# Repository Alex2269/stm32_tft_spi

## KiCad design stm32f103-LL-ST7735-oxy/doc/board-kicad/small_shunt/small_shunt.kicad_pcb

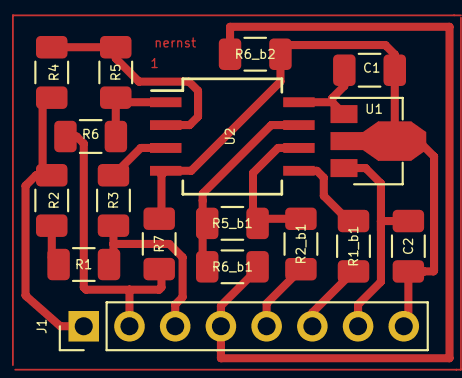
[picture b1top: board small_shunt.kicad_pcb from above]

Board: 2 copper layers, 17 parts (0 on the bottom side), 16 nets.

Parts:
C1, C2: C_Small; R_1206_3216Metric
J1: Conn_01x08; PinHeader_1x08_P2.54mm_Vertical
R1, R1_b1, R2, R2_b1, R3, R4, R5, R5_b1, R6, R6_b1, R6_b2, R7: R; R_1206_3216Metric
U1: L78L33_SOT89; SOT-89-3
U2: MCP602; SO-8_5.3x6.2mm_P1.27mm

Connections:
GND: C1.2, C2.2, J1.8, R6_b2.1, R7.1, U1.2, U2.4
unnamed: C1.1, U1.1, U2.8
unnamed: C2.1, J1.7, U1.3
unnamed: J1.1, R2.1, R4.2
unnamed: J1.2, R6.1, R7.2
unnamed: J1.3, R1.2, R3.2
unnamed: J1.4, R6_b1.1, R6_b2.2
unnamed: J1.5, R2_b1.2
unnamed: J1.6, R1_b1.2
unnamed: R1.1, R2.2
unnamed: R1_b1.1, U2.5
unnamed: R2_b1.1, R5_b1.1, U2.6
unnamed: R3.1, U2.3
unnamed: R4.1, R5.2, U2.2
unnamed: R5.1, R6.2, U2.1
unnamed: R5_b1.2, R6_b1.2, U2.7

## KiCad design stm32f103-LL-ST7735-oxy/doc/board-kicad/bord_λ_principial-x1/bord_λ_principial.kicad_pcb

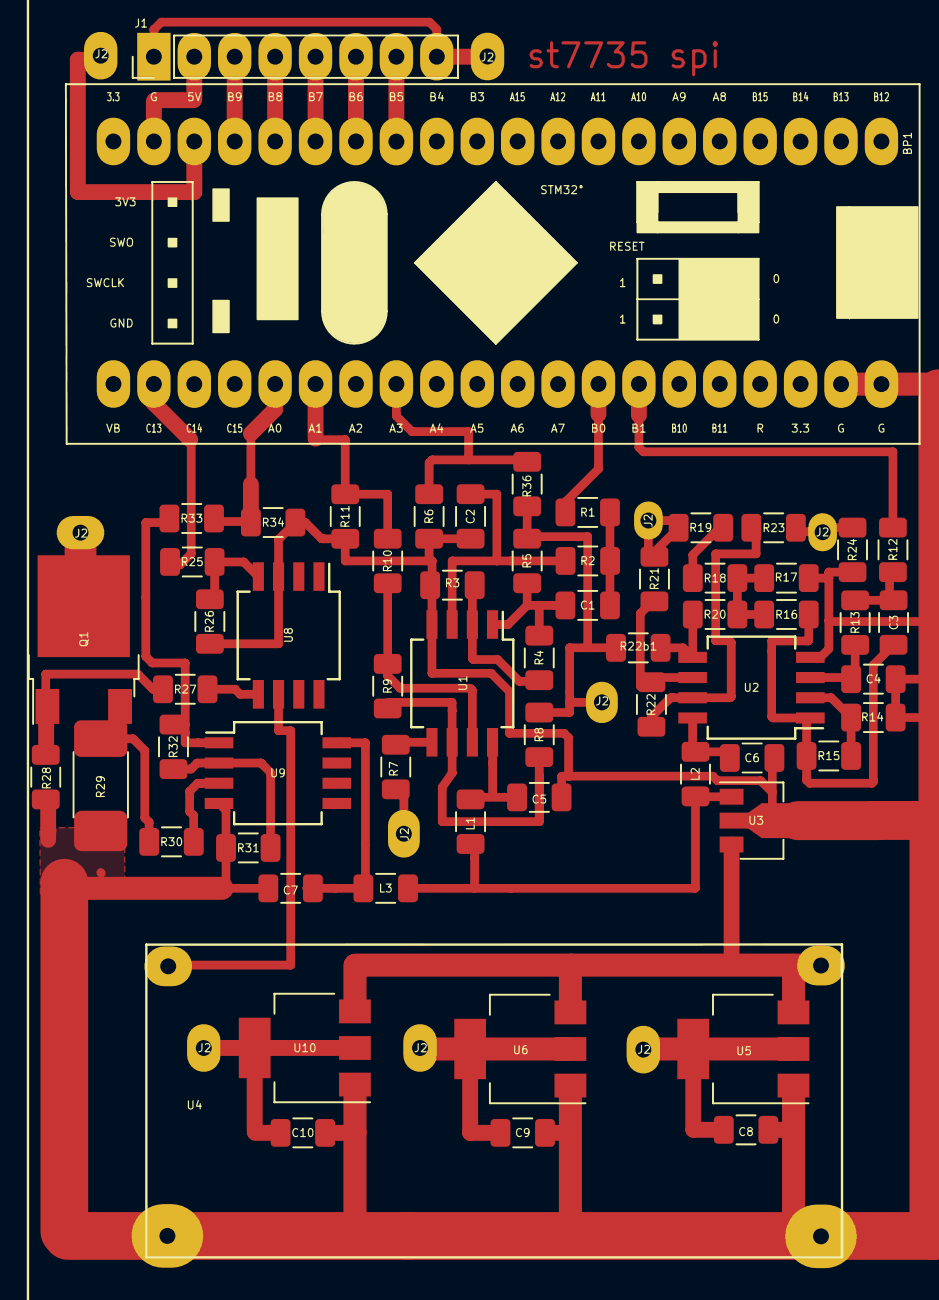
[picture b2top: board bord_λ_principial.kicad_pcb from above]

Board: 2 copper layers, 71 parts (0 on the bottom side), 48 nets.

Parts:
BP1: BluePill_1; YAAJ_BluePill
C1, C2, C3, C4: 1mf; R_1206_3216Metric
C5, C6, C7, C8, C9, C10: 1uF; R_1206_3216Metric
J1: Conn_01x08_Male; PinHeader_1x08_P2.54mm_Vertical
J2, J2#2, J2#3, J2#4, J2#5, J2#6, J2#7, J2#8, J2#9, J2#10: Conn_01x01_Female; MountingHole_2.2mm_M2_DIN965_Pad
L1, L2, L3: 10uG; L_1206_3216Metric
Q1: LR7843; TO-252-2
R1, R2, R3, R7, R8, R12, R13, R14, R20, R21: 43k; R_1206_3216Metric
R4, R6, R15, R17, R26, R28, R36: 22k; R_1206_3216Metric
R5: 10; R_1206_3216Metric
R9: 100; R_1206_3216Metric
R10, R23, R33: 3k3; R_1206_3216Metric
R11, R24, R34: 6k8; R_1206_3216Metric
R16: 240R; R_1206_3216Metric
R18, R19: 31R; R_1206_3216Metric
R22, R22b1: 100k*; R_1206_3216Metric
R25: 1K; R_1206_3216Metric
R27: 0.1K; R_1206_3216Metric
R29: 0.01R; R_2512_6332Metric
R30: 1k; R_1206_3216Metric
R31: 1k*; R_1206_3216Metric
R32: 47k; R_1206_3216Metric
U1, U2, U9: MCP602; SO-8_5.3x6.2mm_P1.27mm
U3: L78L05_SOT89; SOT-89-3
U4: lm2596-hw-411
U5: AMS1117-3.3; SOT-223-3_TabPin2
U6: AMS1117-5.0; SOT-223-3_TabPin2
U8: IR4427; SO-8_5.3x6.2mm_P1.27mm
U10: LM1117-2.5; SOT-223-3_TabPin2

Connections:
+2V5: C10.2, U10.2
+3V3: C8.2, J1.1, J1.8, U5.2
+5P: L1.1, L2.1, L3.1, U3.1
+5V: BP1.18, C9.2, U6.2
+7.5V: U3.3, U4.3, U5.3, U6.3, U10.3
+12V: U4.1, U8.6
GND: BP1.39, BP1.40, C2.1, C4.1, C5.1, C6.1, C7.1, C8.1, C9.1, C10.1, R3.1, R6.1, R11.2, R14.1, R17.1, R24.2, R26.2, R28.2, R29.2, R31.2, R34.1, U1.4, U2.4, U3.2, U4.2, U4.4, U5.1, U6.1, U8.3, U9.4, U10.1
unnamed: BP1.13, J1.7
unnamed: BP1.14, J1.6
unnamed: BP1.15, J1.5
unnamed: BP1.16, J1.4
unnamed: BP1.17, J1.3
unnamed: BP1.19, J1.2
unnamed: BP1.22, R25.1
unnamed: BP1.25, R33.1, R34.2
unnamed: BP1.26, R10.2, R11.1
unnamed: BP1.27, R23.2, R24.1
unnamed: BP1.28, R6.2, R36.2
unnamed: BP1.33, R1.2
unnamed: BP1.34, R12.2
unnamed: C1.1, R4.1, R5.2, U1.1
unnamed: C1.2, R1.1, R2.2
unnamed: C2.2, R2.1, U1.3
unnamed: C3.1, R15.1, R16.2, U2.1
unnamed: C3.2, R12.1, R13.2
unnamed: C4.2, R13.1, U2.3
unnamed: C5.2, L1.2, U1.8
unnamed: C6.2, L2.2, U2.8
unnamed: C7.2, L3.2, U9.8
unnamed: R19.1, R21.1
unnamed: R5.1, R8.1, R22b1.2, R36.1
unnamed: Q1.1, R27.1, R28.1
unnamed: Q1.3, R29.1, R30.2
unnamed: R3.2, R4.2, U1.2
unnamed: R7.2, U1.5
unnamed: R8.2, R9.1, U1.6
unnamed: R9.2, R10.1, U1.7
unnamed: R14.2, R15.2, U2.2
unnamed: R16.1, R17.2, R18.2, R20.1
unnamed: R18.1, R19.2
unnamed: R20.2, R22b1.1, U2.5
unnamed: R21.2, R22.1, U2.6
unnamed: R22.2, R23.1, U2.7
unnamed: R25.2, R26.1, U8.4
unnamed: R27.2, U8.5
unnamed: R30.1, U9.3
unnamed: R31.1, R32.2, U9.2
unnamed: R32.1, R33.2, U9.1

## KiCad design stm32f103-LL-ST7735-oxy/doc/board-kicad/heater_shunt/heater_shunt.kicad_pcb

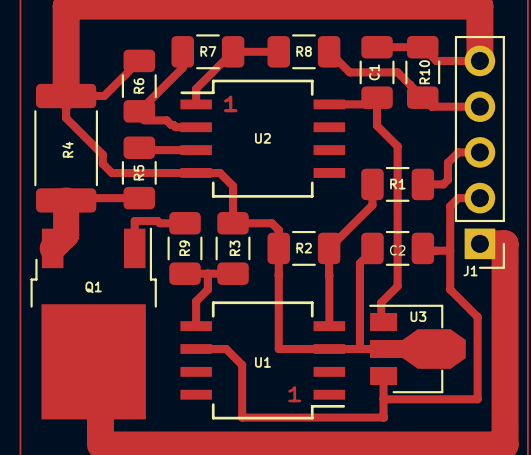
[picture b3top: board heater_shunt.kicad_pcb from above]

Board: 2 copper layers, 17 parts (0 on the bottom side), 13 nets.

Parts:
C1, C2: C_Small; R_1206_3216Metric
J1: Conn_01x05; PinHeader_1x05_P2.54mm_Vertical
Q1: Q_NMOS_GDS; TO-252-2
R1, R2, R3, R5, R6, R7, R8, R9, R10: R; R_1206_3216Metric
R4: R; R_2512_6332Metric
U1: IR4427; SO-8_5.3x6.2mm_P1.27mm
U2: MCP602; SO-8_5.3x6.2mm_P1.27mm
U3: L78L33_SOT89; SOT-89-3

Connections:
unnamed: C1.1, U2.8, U3.1
unnamed: C1.2, C2.2, J1.5, R2.2, R3.2, R4.1, R6.2, R10.1, U1.3, U2.4, U3.2
unnamed: C2.1, J1.2, U1.6, U3.3
unnamed: J1.1, Q1.2
unnamed: J1.3, R1.1
unnamed: J1.4, R8.1, R10.2
unnamed: Q1.1, R9.1
unnamed: Q1.3, R4.2, R5.2
unnamed: R1.2, R2.1, U1.4
unnamed: R3.1, R9.2, U1.5
unnamed: R5.1, U2.3
unnamed: R6.1, R7.2, U2.2
unnamed: R7.1, R8.2, U2.1

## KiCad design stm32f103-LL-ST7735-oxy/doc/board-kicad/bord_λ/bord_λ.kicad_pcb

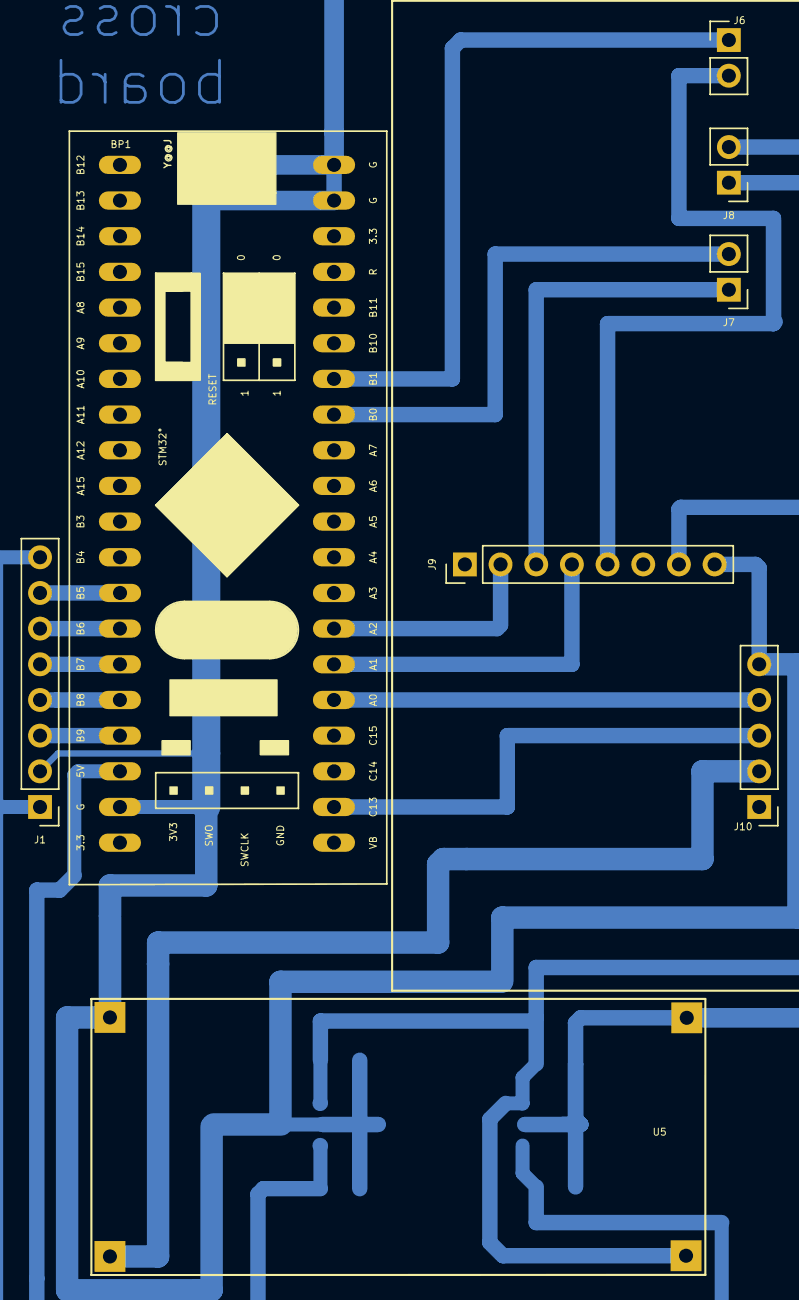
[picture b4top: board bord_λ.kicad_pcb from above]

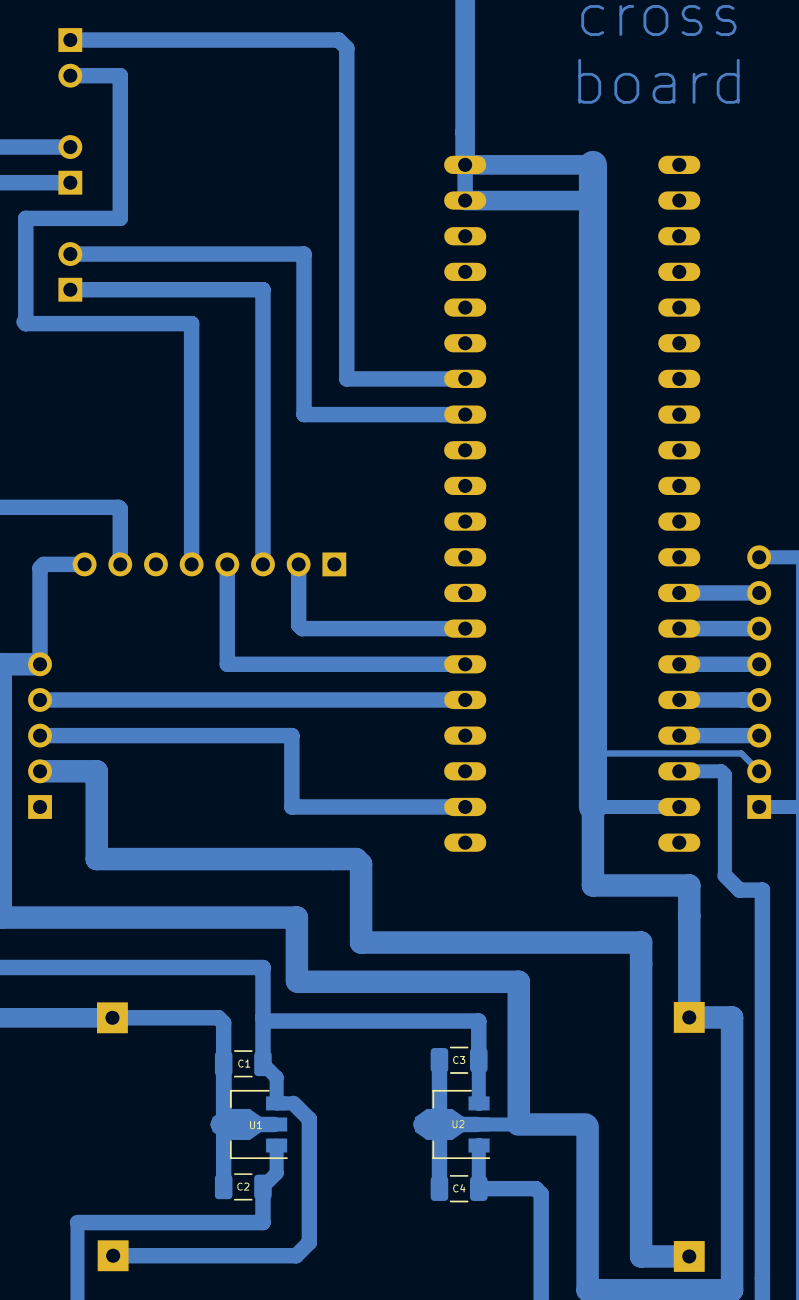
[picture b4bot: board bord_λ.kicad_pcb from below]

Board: 2 copper layers, 14 parts (6 on the bottom side), 18 nets.

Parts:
BP1: BluePill_1; YAAJ_BluePill
C1, C2, C3, C4: C; C_1206_3216Metric
J1, J9: Conn_01x08_Female; PinHeader_1x08_P2.54mm_Vertical
J6, J7, J8: Conn_01x02_Female; PinHeader_1x02_P2.54mm_Vertical
J10: Conn_01x05_Female; PinHeader_1x05_P2.54mm_Vertical
U1: L78L33_SOT89; SOT-89-3
U2: L78L05_SOT89; SOT-89-3
U5: lm2596-hw-411

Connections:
+3V3: C2.1, J1.1, J1.8, U1.1
+5V: BP1.18, C4.1, U2.1
+6V: C1.1, C3.1, J8.1, J9.7, U1.3, U2.3, U5.1
+12V: J10.2, U5.3
GND: BP1.19, BP1.39, BP1.40, C1.2, C2.2, C3.2, C4.2, J1.2, J8.2, J9.8, J10.5, U1.2, U2.2, U5.2, U5.4
unnamed: BP1.13, J1.7
unnamed: BP1.14, J1.6
unnamed: BP1.15, J1.5
unnamed: BP1.16, J1.4
unnamed: BP1.17, J1.3
unnamed: BP1.22, J10.3
unnamed: BP1.25, J10.4
unnamed: BP1.26, J9.4
unnamed: BP1.27, J9.2
unnamed: BP1.33, J7.2
unnamed: BP1.34, J6.1
unnamed: J6.2, J9.5
unnamed: J7.1, J9.3

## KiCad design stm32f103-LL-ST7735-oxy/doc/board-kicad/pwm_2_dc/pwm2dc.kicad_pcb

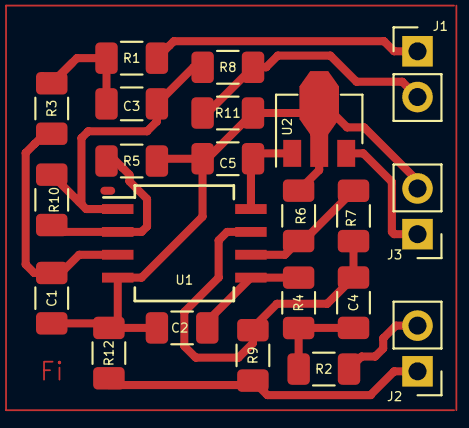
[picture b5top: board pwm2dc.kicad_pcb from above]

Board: 2 copper layers, 22 parts (0 on the bottom side), 15 nets.

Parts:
C1, C2, C3, C4, C5: C_Small; R_1206_3216Metric
J1, J2, J3: Conn_01x02; PinHeader_1x02_P2.54mm_Vertical
R1, R2, R3, R4, R5, R6, R7, R8, R9, R10, R11, R12: R_Small; R_1206_3216Metric
U1: MCP602; SO-8_5.3x6.2mm_P1.27mm
U2: L78L33_SOT89; SOT-89-3

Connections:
unnamed: C1.1, R3.1, U1.3
unnamed: C1.2, C2.2, C5.2, J3.2, R5.2, R6.2, R11.2, R12.1, U1.4, U2.2
unnamed: C2.1, R4.1, U1.5
unnamed: C3.1, R8.2, R10.1, U1.1
unnamed: C3.2, R1.1, R3.2
unnamed: C4.1, R7.1, R9.2, U1.7
unnamed: C4.2, R2.1, R4.2
unnamed: C5.1, U1.8, U2.1
unnamed: J1.1, R1.2
unnamed: J1.2, R8.1, R11.1
unnamed: J2.1, R9.1, R12.2
unnamed: J2.2, R2.2
unnamed: J3.1, U2.3
unnamed: R6.1, R7.2, U1.6
unnamed: R5.1, R10.2, U1.2

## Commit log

2021-03-08 2021-03-08
2021-03-30 2021-03-31
2021-04-04 2021-04-04
